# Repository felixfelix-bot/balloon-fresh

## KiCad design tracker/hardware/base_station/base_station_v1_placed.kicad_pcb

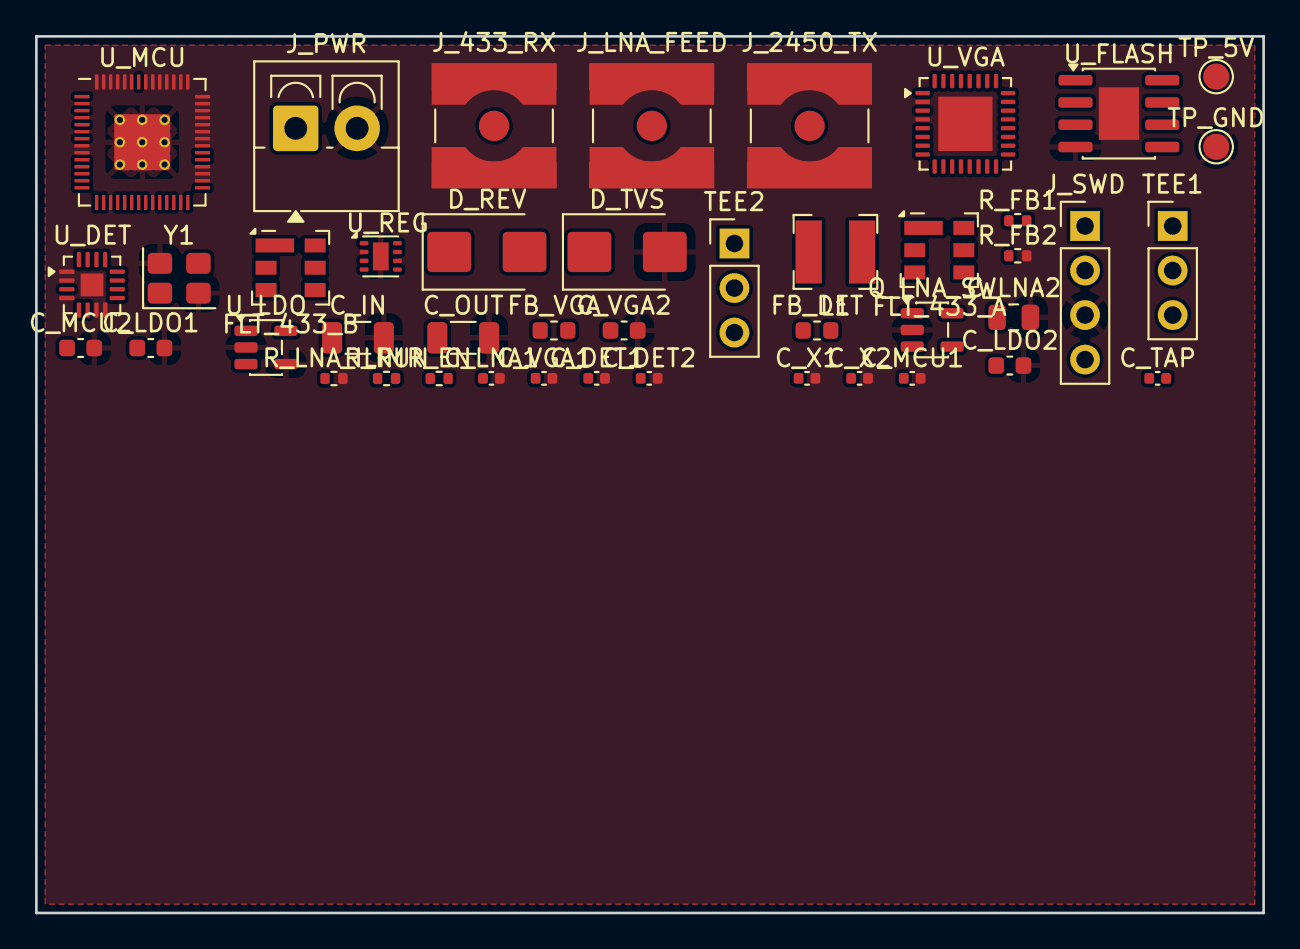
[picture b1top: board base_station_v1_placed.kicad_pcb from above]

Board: 4 copper layers, 70.0 x 50.0 mm, 44 parts (0 on the bottom side), 35 nets, no tracks yet.

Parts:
C_DET1: 100nF; C_0402_1005Metric
C_DET2: 100nF (VOUT filter); C_0402_1005Metric
C_IN: 10uF 25V; C_1206_3216Metric
C_LDO1, C_LDO2: 1uF; C_0603_1608Metric
C_LNA1: 100nF (tee DC injection bypass); C_0402_1005Metric
C_LNA2: 10uF (tee DC injection bypass); C_0805_2012Metric
C_MCU1: 100nF; C_0402_1005Metric
C_MCU2: 1uF; C_0603_1608Metric
C_OUT: 22uF 6V3; C_1206_3216Metric
C_TAP: directional/coupled tap after the BPF/LNA (TODO(u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; C_0402_1005Metric
C_VGA1: 100nF; C_0402_1005Metric
C_VGA2: 1uF; C_0603_1608Metric
C_X1, C_X2: 15pF; C_0402_1005Metric
D_REV: reverse-polarity/TVS protection; D_SMB
D_TVS: TVS clamp (set point TODO(unverified)); D_SMB
FB_DET: ferrite bead; L_0603_1608Metric
FB_VGA: ferrite bead / pi filter; L_0603_1608Metric
FLT_433_A: 433 MHz BPF (ahead of LNA); Filter_SAW-6_3.8x3.8mm
FLT_433_B: 433 MHz BPF #2 (before the AD8318 -- mandatory); Filter_SAW-6_3.8x3.8mm
J_433_RX: 433 MHz RX antenna port (SMA); SMA_Amphenol_132134-10_Vertical
J_2450_TX: 2.45 GHz TX antenna port (SMA; no PA on the PCBA); SMA_Amphenol_132134-10_Vertical
J_LNA_FEED: coax feed to the masthead LNA (SMA); SMA_Amphenol_132134-10_Vertical
J_PWR: VIN_GS 9-18V input; TerminalBlock_4Ucon_1x02_P3.50mm_Vertical
J_SWD: SWD debug header 1x4; PinHeader_1x04_P2.54mm_Vertical
L1: 2.2uH buck inductor; L_Bourns-SRN4018
Q_LNA_SW: load switch / resettable limiter (ADL5240 must NO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; SOT-23-5
R_EN: 100k LDO/REG enable pull-up; R_0402_1005Metric
R_FB1: 100k (feedback divider); R_0402_1005Metric
R_FB2: 22.6k (feedback divider); R_0402_1005Metric
R_LNA_ILIM: set LNA branch current limit; R_0402_1005Metric
R_RUN: 10k RUN pull-up; R_0402_1005Metric
TEE1: Mini-Circuits ZFBT-4R2GW+ bias tee (masthead feed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; PinHeader_1x03_P2.54mm_Vertical
TEE2: ZFBT-4R2GW+ bias tee (board side); PinHeader_1x03_P2.54mm_Vertical
TP_5V: +5V_PCBA test point; TestPoint_Pad_D1.5mm
TP_GND: GND test point; TestPoint_Pad_D1.5mm
U_DET: AD8318ACPZ-R7 log detector (15mA allowance); LFCSP-16-1EP_3x3mm_P0.5mm_EP1.3x1.3mm
U_FLASH: QSPI flash (RP2040 boot); SOIC-8-1EP_3.9x4.9mm_P1.27mm_EP2.29x3mm
U_LDO: 3.3V LDO for +3V3_MCU; SOT-23-5
U_MCU: RP2040 QFN-56; RP2040-QFN-56
U_REG: TPS62162 5V buck (3-17V in, 1A out); WSON-8-1EP_2x2mm_P0.5mm_EP0.9x1.6mm
U_VGA: ADL5240 VGA (93mA @ 4.75-5.25V, gain from RP2040); LFCSP-32-1EP_5x5mm_P0.5mm_EP3.1x3.1mm
Y1: 12MHz crystal; Crystal_SMD_3225-4Pin_3.2x2.5mm

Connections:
+3V3_MCU: C_LDO1.1, J_SWD.1, R_RUN.1, U_FLASH.8, U_LDO.5, U_MCU.16
+5V_DET: C_DET1.1, FB_DET.2, U_DET.5
+5V_LNA_SW: C_LNA1.1, C_LNA2.1, Q_LNA_SW.5, TEE1.3, TEE2.3
+5V_PCBA: C_LDO2.1, C_OUT.1, FB_DET.1, FB_VGA.1, L1.2, Q_LNA_SW.1, R_EN.1, R_FB1.1, TP_5V.1, U_LDO.1, U_REG.5
+5V_VGA: C_VGA1.1, C_VGA2.1, FB_VGA.2, U_VGA.1
DET_RF_IN: FLT_433_B.2, U_DET.3
DET_VOUT: C_DET2.1, U_DET.6, U_MCU.7
GND: C_DET1.2, C_DET2.2, C_IN.2, C_LDO1.2, C_LDO2.2, C_LNA1.2, C_LNA2.2, C_MCU1.2, C_MCU2.2, C_OUT.2, C_VGA1.2, C_VGA2.2, C_X1.2, C_X2.2, D_TVS.2, J_433_RX.2, J_2450_TX.2, J_LNA_FEED.2, J_PWR.2, J_SWD.3, Q_LNA_SW.2, R_FB2.2, R_LNA_ILIM.2, TP_GND.1, U_DET.1, U_DET.2, U_DET.4, U_DET.7, U_DET.8, U_DET.17, U_FLASH.4, U_FLASH.9, U_LDO.2, U_LDO.4, U_MCU.2, U_MCU.4, U_MCU.6, U_MCU.8, U_MCU.9, U_MCU.17, U_MCU.23, U_MCU.27, U_MCU.30, U_MCU.31, U_MCU.32, U_MCU.35, U_MCU.36, U_MCU.37, U_MCU.38, U_MCU.39, U_MCU.40, U_MCU.41, U_MCU.42, U_MCU.43, U_MCU.44, U_MCU.45, U_MCU.46, U_MCU.47, U_MCU.48, U_MCU.49, U_MCU.51, U_MCU.52, U_MCU.53, U_MCU.54, U_MCU.55, U_MCU.56, U_MCU.57, U_REG.2, U_REG.6, U_REG.9, U_VGA.2, U_VGA.4, U_VGA.33, Y1.2, Y1.4
IOVDD: C_MCU1.1, C_MCU2.1, U_MCU.1, U_MCU.5
LNA_EN: Q_LNA_SW.3, U_MCU.21
LNA_FLT: Q_LNA_SW.4, R_LNA_ILIM.1, U_MCU.22
QSPI_SCLK: U_FLASH.6, U_MCU.11
QSPI_SD0: U_FLASH.2, U_MCU.12
QSPI_SD1: U_FLASH.5, U_MCU.13
QSPI_SD2: U_FLASH.3, U_MCU.14
QSPI_SD3: U_FLASH.7, U_MCU.15
QSPI_SS: U_FLASH.1, U_MCU.10
REG_EN: R_EN.2, U_REG.7
REG_FB: R_FB1.2, R_FB2.1, U_REG.4
REG_PG: U_MCU.50, U_REG.8
REG_SW: L1.1, U_REG.3
RF_433_ANT: FLT_433_A.1, J_433_RX.1
RF_433_BPF1: FLT_433_A.2, TEE1.1
RF_TAP: C_TAP.2, FLT_433_B.1
RUN: R_RUN.2, U_MCU.26
SWCLK: J_SWD.4, U_MCU.28
SWDIO: J_SWD.2, U_MCU.29
VGA_GAIN0: U_MCU.18, U_VGA.6
VGA_GAIN1: U_MCU.19, U_VGA.7
VGA_GAIN2: U_MCU.20, U_VGA.8
VGA_RF_IN: C_TAP.1, TEE2.2, U_VGA.3
VIN_GS: D_REV.2, J_PWR.1
VIN_GS_PROT: C_IN.1, D_REV.1, D_TVS.1, U_REG.1
XIN: C_X1.1, U_MCU.24, Y1.1
XOUT: C_X2.1, U_MCU.25, Y1.3

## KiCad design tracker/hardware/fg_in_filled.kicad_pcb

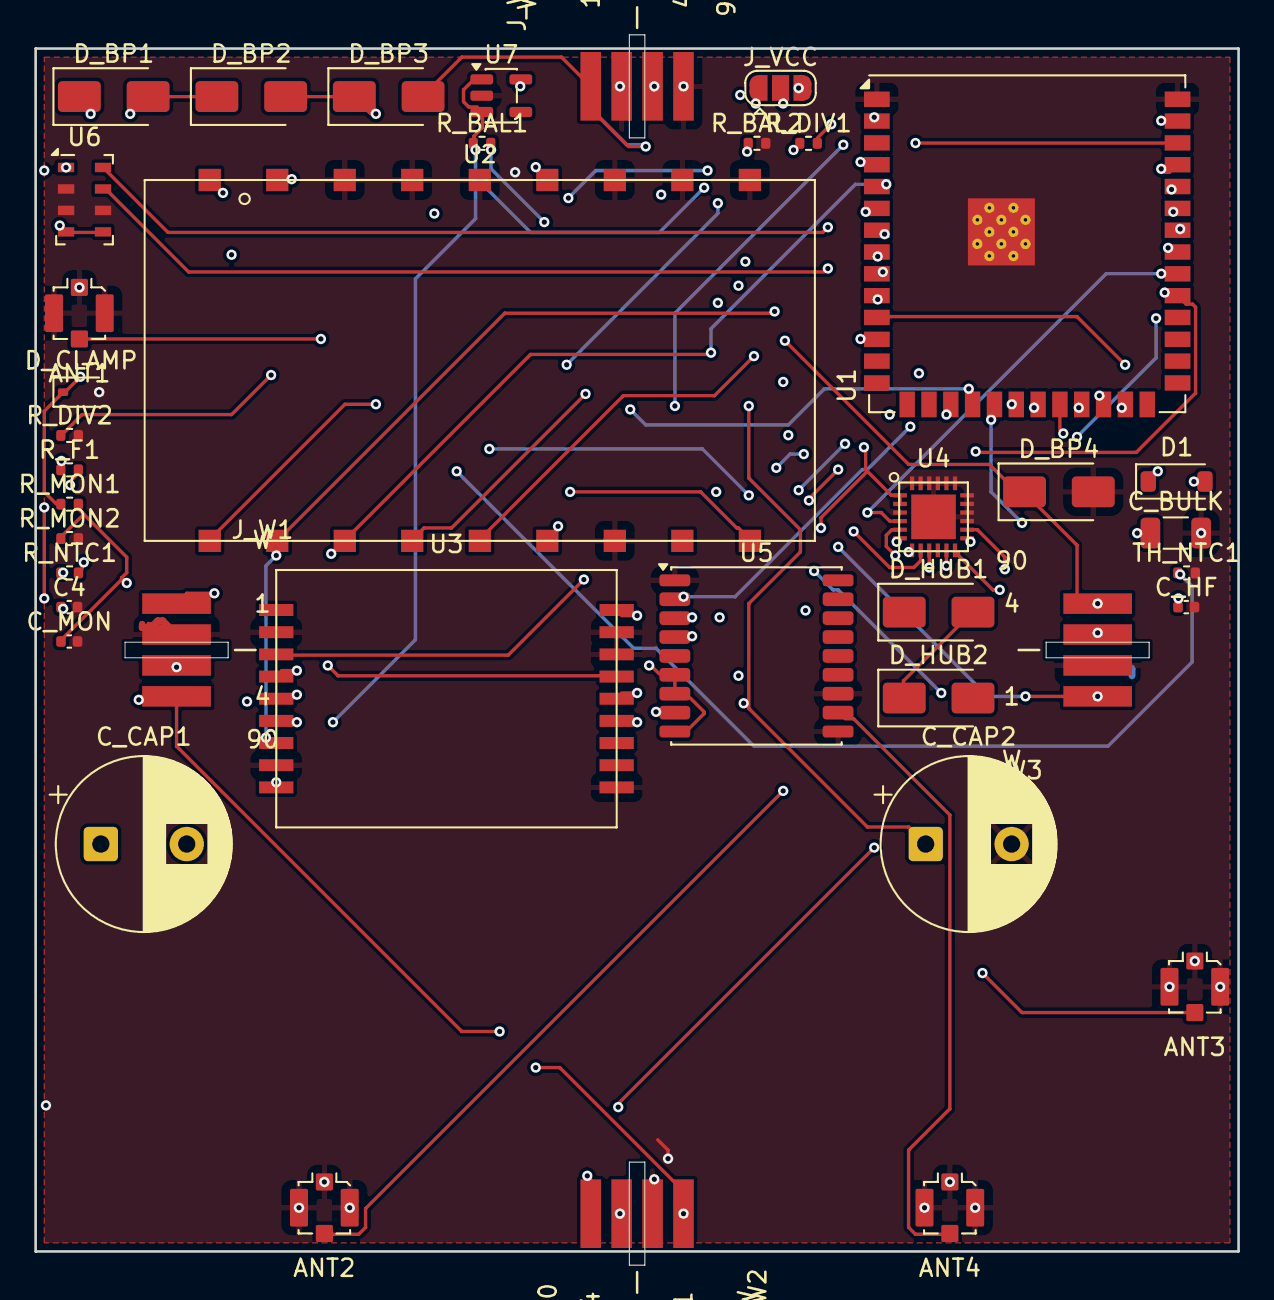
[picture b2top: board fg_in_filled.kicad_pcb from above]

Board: 4 copper layers, 70.0 x 71.6 mm, 39 parts (0 on the bottom side), 45 nets.

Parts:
ANT1: U.FL_433_TX; U.FL_Molex_MCRF_73412-0110_Vertical
ANT2: U.FL_2G4_RANGE; U.FL_Molex_MCRF_73412-0110_Vertical
ANT3: U.FL_2G4_RX; U.FL_Molex_MCRF_73412-0110_Vertical
ANT4: U.FL_GNSS_L1; U.FL_Molex_MCRF_73412-0110_Vertical
C4: 10uF; C_0402_1005Metric
C_BULK: 100uF; C_1206_3216Metric
C_CAP1, C_CAP2: 3.3F 2.7V (AVX SCC); CP_Radial_D10.0mm_P5.00mm
C_HF: 100nF; C_0402_1005Metric
C_MON: 10nF; C_0402_1005Metric
D1: BAT54; D_SOD-123
D_BP1, D_BP2, D_BP3, D_BP4: SS24; D_SMA
D_CLAMP: TVS clamp (set point TODO(unverified)); D_SOD-323
D_HUB1, D_HUB2: SS24; D_SMA
J_VCC: F33_VCC_SEL (5V raw | 3V3); SolderJumper-3_P1.3mm_Open_RoundedPad1.0x1.5mm
J_W1: WING_SOCKET_4P (hub wing interface 1); Wing_Tab_4P
J_W2: WING_SOCKET_4P (hub wing interface 2); Wing_Tab_4P
J_W3: WING_SOCKET_4P (hub wing interface 3); Wing_Tab_4P
J_W4: WING_SOCKET_4P (hub wing interface 4); Wing_Tab_4P
R_BAL1, R_BAL2: 10k; R_0402_1005Metric
R_DIV1, R_DIV2: 1M; R_0402_1005Metric
R_F1: 100R; R_0402_1005Metric
R_MON1, R_MON2: 4.7M; R_0402_1005Metric
R_NTC1: TODO(unverified) (sets ntc_r_ratio); R_0402_1005Metric
TH_NTC1: TODO(unverified) (NTC, R25/beta TODO); R_0402_1005Metric
U1: ESP32-S3-WROOM-1U-N8R8; ESP32-S3-WROOM-1U
U2: LoRa2021F33-2G4; LoRa2021F33_2G4
U3: LoRa2021_Castellated
U4: SX1280; SX1280_QFN24
U5: MAX-M10S; ublox_MAX
U6: MS5611-01BA; LGA-8_3x5mm_P1.25mm
U7: TPS7A02; SOT-23-5

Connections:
+3V3: J_VCC.3, R_F1.1, U1.2, U2.5, U3.1, U4.1, U4.2, U5.6, U5.7, U5.9, U6.1, U6.4, U6.5, U7.5
/ANT1_433_TX: ANT1.1, U2.9
/ANT2_2G4_RANGE: ANT2.1, U4.14
/ANT3_2G4_RX: ANT3.1, U3.10
/ANT4_GNSS_L1: ANT4.1, U5.11
/F33_BUSY: U1.12, U2.14
/F33_CS_N: U1.7, U2.13
/F33_IRQ: U1.17, U2.18
/F33_MISO: U1.6, U2.16, U3.3
/F33_MOSI: U1.5, U2.15, U3.4
/F33_RESET_N: U1.18, U2.17
/F33_SCK: U1.4, U2.12, U3.5
/F33_VCC: C_BULK.1, C_HF.1, D_CLAMP.1, J_VCC.2, R_MON1.1, U2.1
/F33_VSENSE: C_MON.1, R_MON1.2, R_MON2.1, U1.21
/GNSS_PPS: U1.23, U5.4
/GNSS_RX: U1.37, U5.3
/GNSS_TX: U1.36, U5.2
/GNSS_VCC: C4.1, R_F1.2, U5.8
/HUB_PV_MID1: D_HUB1.2, D_HUB2.1
/I2C_SCL: U1.38, U6.8
/I2C_SDA: U1.39, U6.7
/NTC_SENSE: R_NTC1.2, TH_NTC1.1
/SCAP_ADC: R_DIV1.2, R_DIV2.1
/SCAP_MID: C_CAP1.2, C_CAP2.1, R_BAL1.2, R_BAL2.1
/SX1280_ANT_SW: U1.35, U4.13
/SX1280_BUSY: U1.31, U4.5
/SX1280_CS_N: U1.10, U4.6
/SX1280_DIO1: U1.33, U4.10
/SX1280_DIO2: U1.11, U4.11
/SX1280_DIO3: U1.34, U4.12
/SX1280_MISO: U1.9, U4.9
/SX1280_MOSI: U1.8, U4.8
/SX1280_RESET_N: U1.32, U4.4
/SX1280_SCK: U1.22, U4.7
/U3_BUSY: U1.24, U3.7
/U3_CS_N: U1.20, U3.6
/U3_IRQ: U1.19, U3.15
/U3_RESET_N: U1.25, U3.14
/VSCAP: C_CAP1.1, D1.1, J_VCC.1, R_BAL1.1, R_DIV1.1, U7.1, U7.3
/VTCXO_VNTC: R_NTC1.1, U3.13
/W1_SOLAR_N: D_BP1.2, D_BP2.1, J_W1.4, J_W2.1
/W1_SOLAR_P: D1.2, D_BP1.1, J_W1.1
/W2_SOLAR_N: D_BP2.2, D_BP3.1, J_W2.4, J_W3.1
/W3_SOLAR_N: D_BP3.2, D_BP4.1, J_W3.4, J_W4.1
GND: ANT1.2, ANT2.2, ANT3.2, ANT4.2, C4.2, C_BULK.2, C_CAP2.2, C_HF.2, C_MON.2, D_BP4.2, D_CLAMP.2, J_W1.2, J_W2.2, J_W3.2, J_W4.2, J_W4.4, R_BAL2.2, R_DIV2.2, R_MON2.2, TH_NTC1.2, U1.1, U1.40, U1.41, U2.2, U2.3, U2.4, U2.6, U2.7, U2.8, U2.11, U3.2, U3.8, U3.11, U3.12, U3.18, U4.3, U4.15, U4.16, U4.17, U4.18, U4.19, U4.20, U4.21, U4.22, U4.23, U4.24, U4.25, U5.1, U5.10, U5.12, U6.2, U6.3, U6.6, U7.2

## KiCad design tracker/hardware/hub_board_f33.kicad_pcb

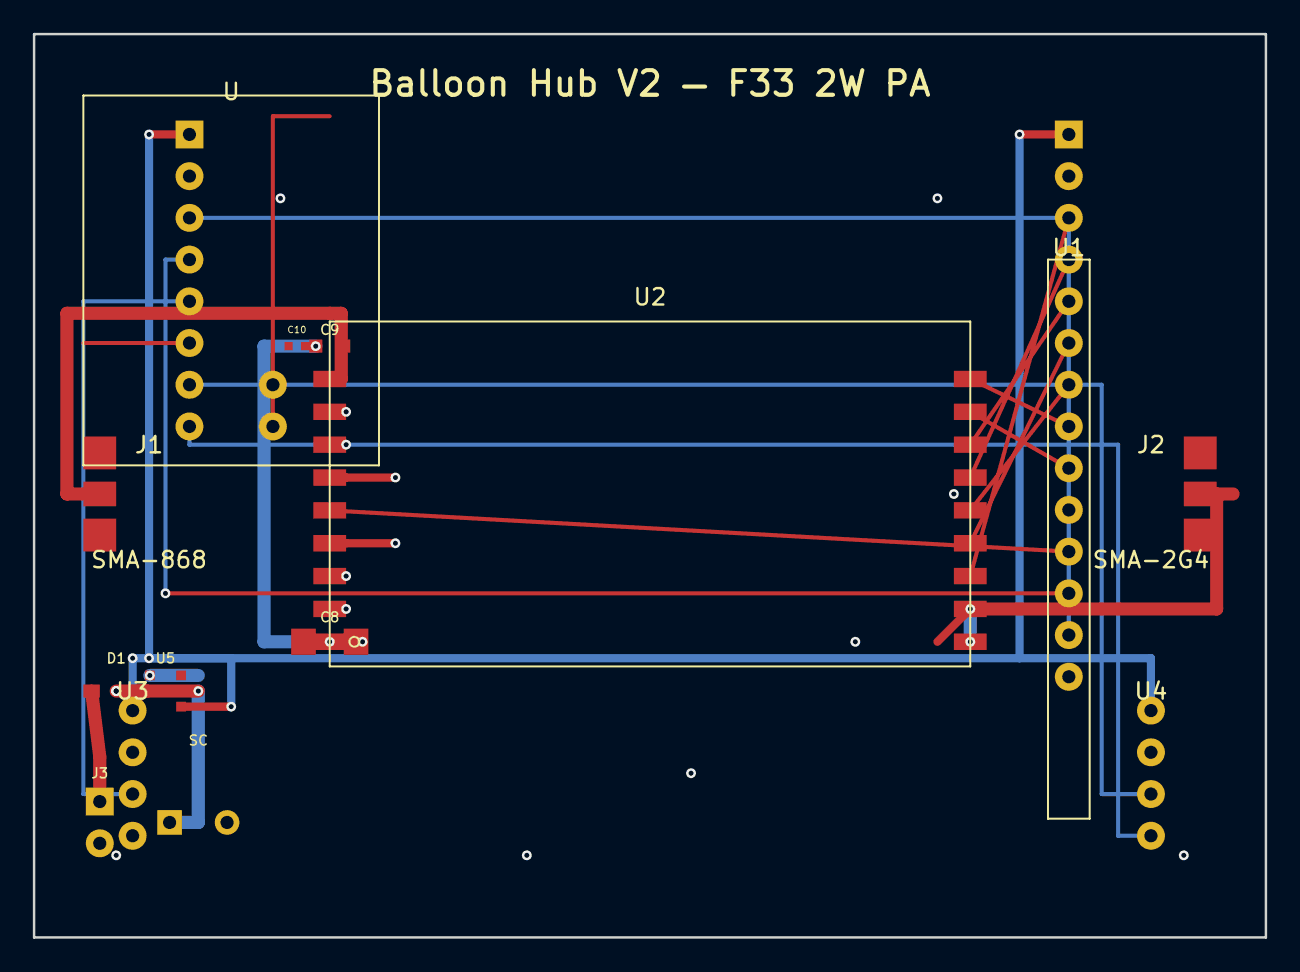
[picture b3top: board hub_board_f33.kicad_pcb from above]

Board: 2 copper layers, 75.0 x 55.0 mm, 14 parts (0 on the bottom side), 19 nets.

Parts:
C8: 100uF; C_1206_3216Metric
C9: 10uF; C_0805_2012Metric
C10: 100nF; C_0402_1005Metric
D1: BAT54; D_SOD-123
J1: SMA-868; SMA_Edge_Mount
J2: SMA-2G4; SMA_Edge_Mount
J3: SOLAR; PinHeader_1x02_P2.54mm_Vertical
SC: 1F 5.5V; CP_Radial_D8.0mm_P3.50mm
U: ESP32-C3-Mini-1; ESP32-C3_Mini_V1_Header
U1: RP2040-Zero; PinHeader_1x14_P2.54mm_Vertical
U2: LoRa2021F33-2G4; LoRa2021F33_2G4
U3: MAX-M10S; PinHeader_1x04_P2.54mm_Vertical
U4: MS5611; PinHeader_1x04_P2.54mm_Vertical
U5: TPS7A02; SOT-23-5

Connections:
3V3: U.1, U1.1, U3.1, U4.1, U5.5
ESP_TX_RP2040_RX: U.3, U1.13
GND: C8.2, C9.2, C10.2, J1.2, J1.3, J2.2, J2.3, J3.2, SC.2, U.2, U1.2, U1.14, U2.2, U2.3, U2.4, U2.6, U2.7, U2.8, U2.11, U3.2, U4.2, U5.2
GPS_TX_ESP_RX: U.5, U3.3
I2C_SCL: U.8, U4.4
I2C_SDA: U.7, U4.3
LR2021_BUSY: U1.7, U2.14
LR2021_CE: U1.11, U2.5
LR2021_IRQ: U1.8, U2.18
LR2021_RST: U1.9, U2.17
RF_2G4_2400: J2.1, U2.10
RF_SUB_868: J1.1, U2.9
RP2040_TX_ESP_RX: U.4, U1.12
SOLAR_IN: D1.1, J3.1
SPI0_MISO: U1.5, U2.16
SPI0_MOSI: U1.4, U2.15
SPI0_NSS: U1.6, U2.13
SPI0_SCK: U1.3, U2.12
VCAP: C8.1, C9.1, C10.1, D1.2, SC.1, U2.1, U5.1, U5.3

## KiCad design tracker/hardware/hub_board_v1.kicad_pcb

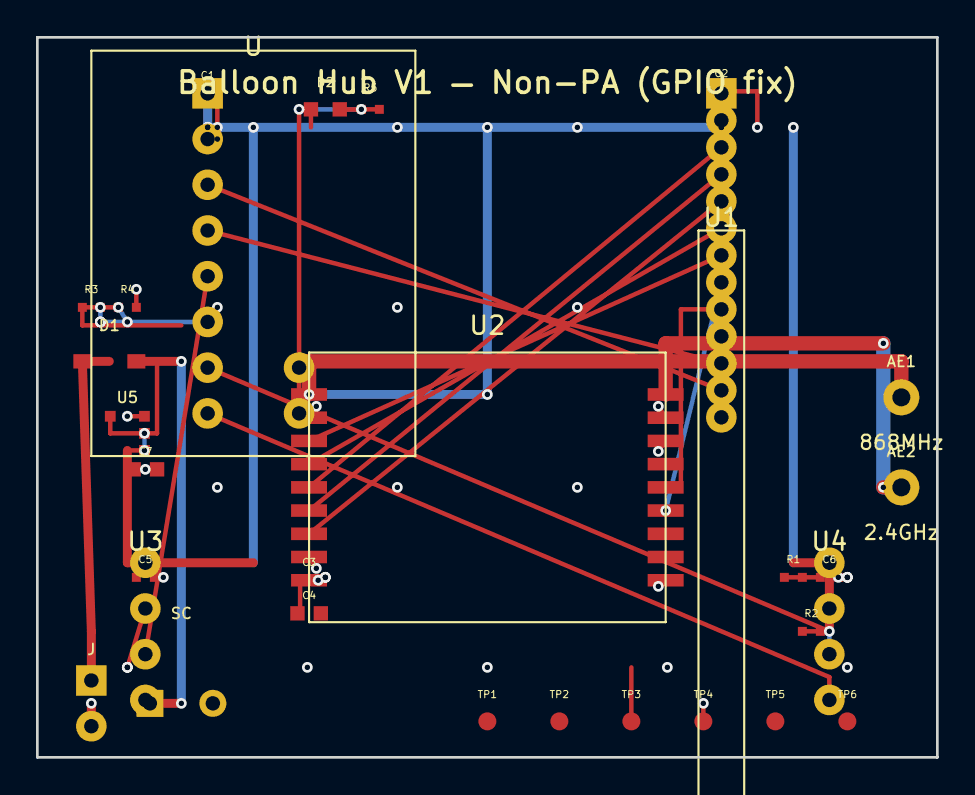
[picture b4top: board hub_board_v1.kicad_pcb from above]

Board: 2 copper layers, 50.0 x 40.0 mm, 30 parts (0 on the bottom side), 21 nets.

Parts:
AE1: 868MHz; TestPoint_THTPad_D2.0mm_Drill1.0mm
AE2: 2.4GHz; TestPoint_THTPad_D2.0mm_Drill1.0mm
C1, C2, C3, C5, C6: 100nF; C_0402_1005Metric
C4, C7: 10uF; C_0805_2012Metric
D1: BAT54; D_SOD-123
D2: STATUS; LED_0603_1608Metric
J: SOLAR; PinHeader_1x02_P2.54mm_Vertical
R1, R2: 4.7k; R_0402_1005Metric
R3, R4: 1M; R_0402_1005Metric
R5: 330R; R_0402_1005Metric
SC: 1F 5.5V; CP_Radial_D8.0mm_P3.50mm
TP1: SPI0_SCK; TestPoint_Pad_D1.0mm
TP2: SPI0_MOSI; TestPoint_Pad_D1.0mm
TP3: 3V3; TestPoint_Pad_D1.0mm
TP4: GND; TestPoint_Pad_D1.0mm
TP5: LED_GPIO18; TestPoint_Pad_D1.0mm
TP6: FEM_TX_GPIO19; TestPoint_Pad_D1.0mm
U: ESP32-C3-Mini-1; ESP32-C3_Mini_V1_Header
U1: RP2040-Zero; PinHeader_1x13_P2.54mm_Vertical
U2: LoRa2021; LoRa2021_Castellated
U3: MAX-M10S; PinHeader_1x04_P2.54mm_Vertical
U4: MS5611; PinHeader_1x04_P2.54mm_Vertical
U5: TPS7A02; SOT-23-5

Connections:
3V3: C1.1, C2.1, C3.1, C4.1, C5.1, C6.1, C7.1, R1.1, R2.1, TP3.1, U.1, U1.1, U2.1, U3.1, U4.1, U5.5
ESP_TX_RP2040_RX: U.3, U1.12
GND: C1.2, C2.2, C3.2, C4.2, C5.2, C6.2, C7.2, D2.1, J.2, R4.2, SC.2, TP4.1, U.2, U1.2, U1.13, U2.2, U2.8, U2.11, U2.12, U2.18, U3.2, U4.2, U5.2
GPS_TX_ESP_RX: U.5, U3.3
I2C_SCL: R2.2, U.8, U4.4
I2C_SDA: R1.2, U.7, U4.3
LED_ANODE: D2.2, R5.2
LR2021_BUSY: U1.7, U2.7
LR2021_DIO9: U1.8, U2.15
LR2021_RST: U1.9, U2.14
RF_2G4_2400: AE2.1, U2.10
RF_SUB_868: AE1.1, U2.9
RP2040_TX_ESP_RX: U.4, U1.11
SOLAR_IN: D1.1, J.1
SPI0_MISO: U1.5, U2.3
SPI0_MOSI: TP2.1, U1.4, U2.4
SPI0_NSS: U1.6, U2.6
SPI0_SCK: TP1.1, U1.3, U2.5
STATUS_LED: R5.1, TP5.1
VCAP: D1.2, R3.1, SC.1, U5.1, U5.3
VDIV_MID: R3.2, R4.1, U.6
